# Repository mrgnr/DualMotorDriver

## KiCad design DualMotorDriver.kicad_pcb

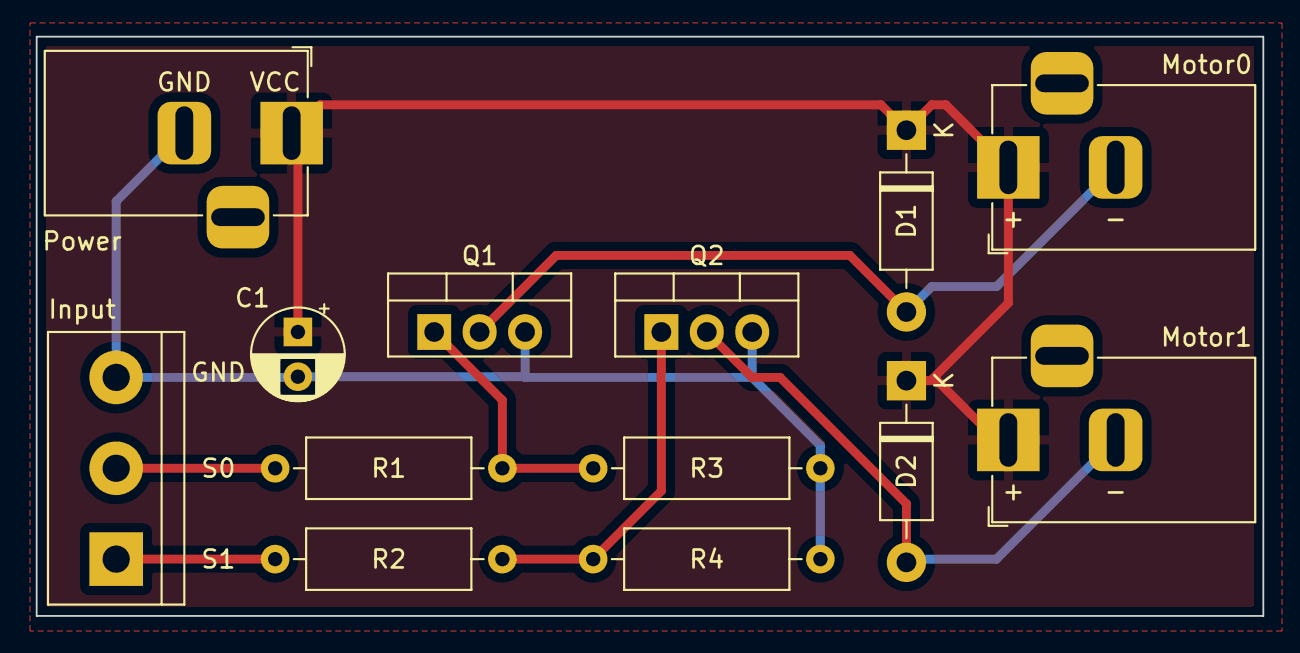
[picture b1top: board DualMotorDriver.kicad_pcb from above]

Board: 2 copper layers, 68.6 x 32.4 mm, 13 parts (0 on the bottom side), 8 nets.

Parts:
C1: 0.47 uF; CP_Radial_D5.0mm_P2.50mm
D1, D2: 1N4001; D_DO-41_SOD81_P10.16mm_Horizontal
Input: Screw_Terminal_01x03; TerminalBlock_bornier-3_P5.08mm
Motor0, Motor1: Barrel_Jack; BarrelJack_Horizontal
Power: Barrel_Jack; BarrelJack_Horizontal
Q1, Q2: IRLZ34N; TO-220-3_Vertical
R1, R2: 220; R_Axial_DIN0309_L9.0mm_D3.2mm_P12.70mm_Horizontal
R3, R4: 11K; R_Axial_DIN0309_L9.0mm_D3.2mm_P12.70mm_Horizontal

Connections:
GND: C1.2, Input.3, Power.2, Q1.3 (S), Q2.3 (S), R3.2, R4.2
unnamed: D1.2 (A), Motor0.2, Q1.2 (D)
unnamed: D2.2 (A), Motor1.2, Q2.2 (D)
unnamed: Input.1, R2.1
unnamed: Input.2, R1.1
unnamed: Q1.1 (G), R1.2, R3.1
unnamed: Q2.1 (G), R2.2, R4.1
VCC: C1.1, D1.1 (K), D2.1 (K), Motor0.1, Motor1.1, Power.1

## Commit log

2024-07-12 Initial commit.
